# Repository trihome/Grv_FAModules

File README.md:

# FA Extension boards for Grove System

## 1.Introduction

This repository has an interface board for connecting equipment used in the factory to Seeed Studio's "Grove System".

<http://wiki.seeedstudio.com/Grove_System/>

These modules are used to make the equipment used in the factory (switches, sensors, relays, etc.) Allows you to connect to the GROVE system.

These boards support digital (GPIO), analog, and I2C connection types.

Refer to the READEME file in each directory for more information.

**Note**

Please import this library before using this repository.
<https://github.com/trihome/KiCad_MyLibrary>

**How to make**

[Manual (Japanese only)](https://github.com/trihome/RasPi_PiFA/blob/master/doc/README_pcb.jp.md)

## 2.Line up

|Module|Connection Type |function |
|:---|:---|:---|
|[IOExpander](./IOExpander16ch/)     |I2C     |Isolated input/output via I2C   |
|[DigitalOutput](./DigitalOutput4ch)  |GPIO    |Isolated output  |
|[DigitalInput](./DigitalInput4ch)   |GPIO    |Isolated input   |
|      |    |(We will increase the lineup in the future...)   |
<!--|CurrentSensor  |Analog  |Current measurement using CT  |
|SigTowSensor   |Analog  |Detect tower light status   |
|SimpleUPS      |GPIO    |Manage the power supply to RaspberryPi   |-->

## 3.How to connect to microcomputer board

If your board does not have a Grove connector, obtain a **Grove Expansion Board** to connect your Grove module.

- <http://wiki.seeedstudio.com/Platform/>

### (1)Arduino

- <http://wiki.seeedstudio.com/Base_Shield_V2/>

### (2)Raspberry Pi

- <http://wiki.seeedstudio.com/Grove_Base_Hat_for_Raspberry_Pi/>
- <http://wiki.seeedstudio.com/Grove_Base_Hat_for_Raspberry_Pi_Zero/>

### (3)micro:bit

- <https://www.seeedstudio.com/Grove-Shield-for-micro-bit-v2-0.html>

## 4.License

This is under [CC-BY-SA](https://creativecommons.org/licenses/by-sa/4.0/).

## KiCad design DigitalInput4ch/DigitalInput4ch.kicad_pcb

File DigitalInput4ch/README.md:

# Digital Input 4ch

Digital Input for GROVE Digital.
Isolated inputs.

[Schematic](./img/DigitalInput4ch.pdf)

**Notes**

Please import this library before using this repository.
https://github.com/trihome/KiCad_MyLibrary

## 1.Spec

- 4 isolated inputs.
- [GROVE Digital](https://wiki.seeedstudio.com/Grove_System/#digital) Connector x 2 (2ch x 2 = 4ch)
- Supply 24V power to J5 or J6.
- J3,6 are Input for FA(24V)
  - Recommended Terminal block: [2pin](https://akizukidenshi.com/catalog/g/gP-06307/), [3pin](https://akizukidenshi.com/catalog/g/gP-06308/)
- Selectable Sink(NPN) / Source(PNP) : JP1, JP2
- U1,2,3,4: Photocoupler, you have to choose...

|JP1, JP2|Photocoupler (ex)|
|:--|:--|
|N : Sink(NPN)|[FOD814A300W](https://akizukidenshi.com/catalog/g/gI-06483/), [TLP627](https://akizukidenshi.com/catalog/g/gI-07691/)|
|P : Source(PNP)|[FOD814A300W](https://akizukidenshi.com/catalog/g/gI-06483/)|

## 2.Example of use

<!--
### (1)Terminal block

- Button
  - [IDEC](http://jp.idec.com/ja/p/c10/)
  - [OMRON](https://www.fa.omron.co.jp/products/category/switches/push-buttons_indicator-lamps/)
- Lamp
  - [NIKKEI MFG](http://www.nikkei-mfg.co.jp/product/industry/index.htm)
-->

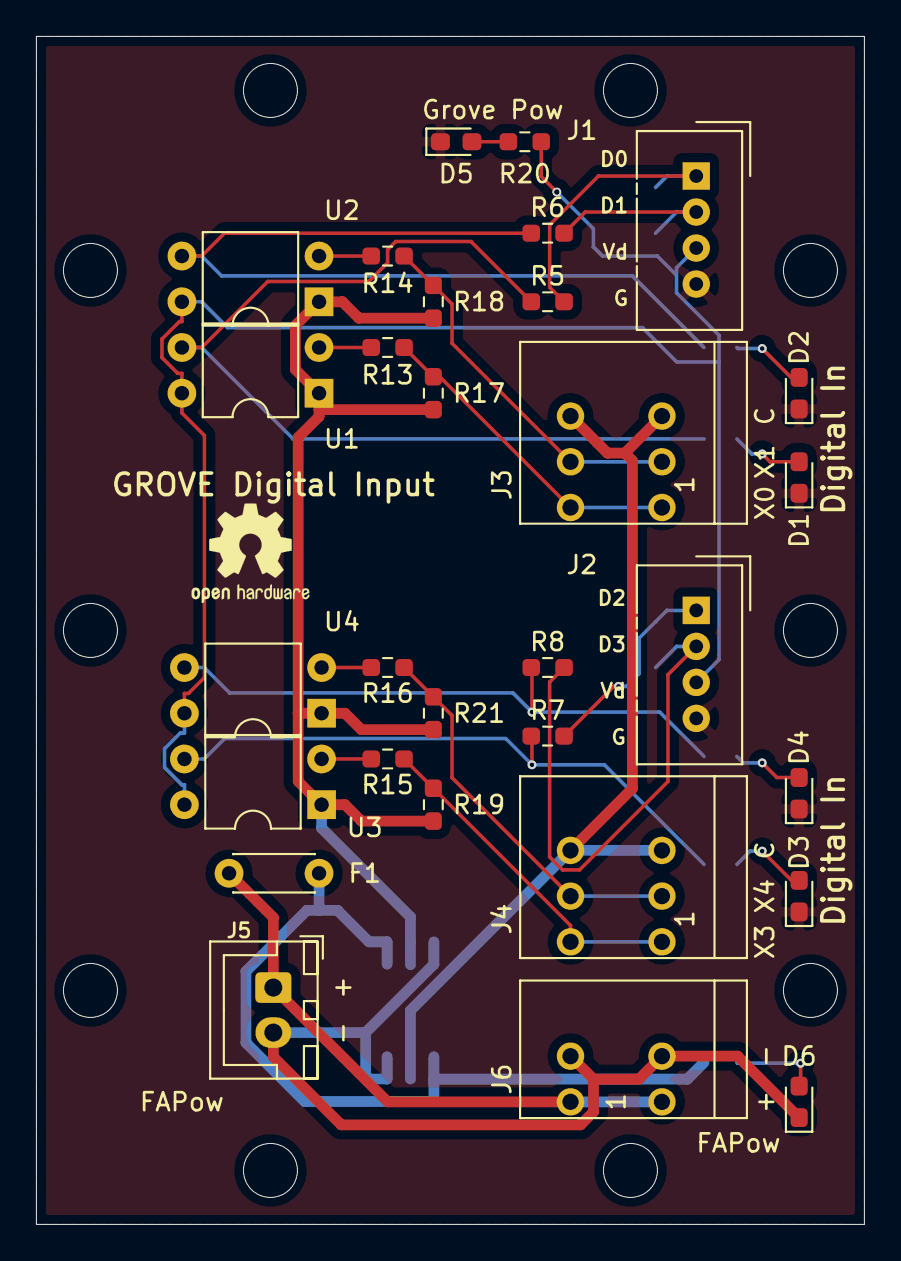
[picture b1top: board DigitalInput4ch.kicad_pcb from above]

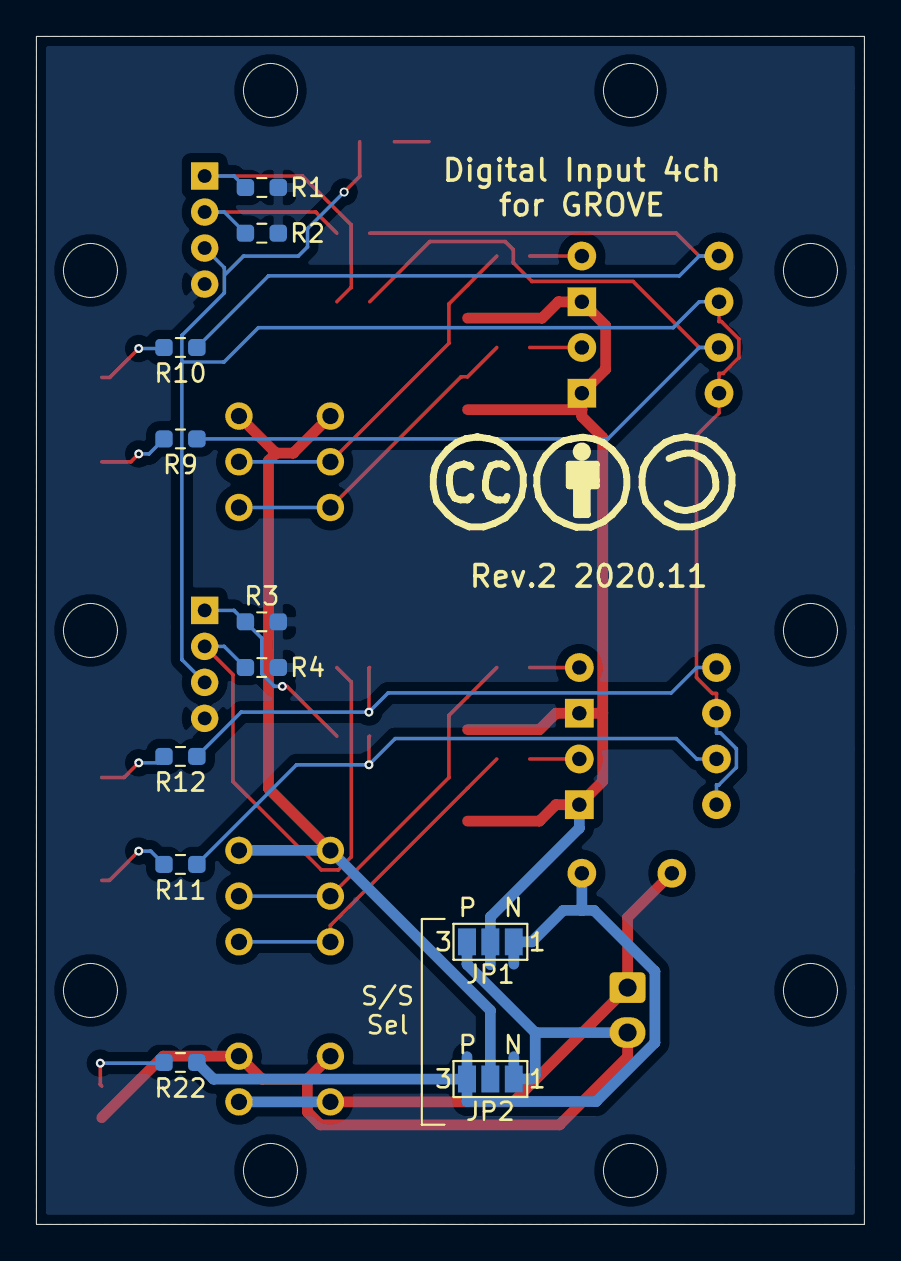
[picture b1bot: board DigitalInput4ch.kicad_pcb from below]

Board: 2 copper layers, 46.0 x 66.0 mm, 53 parts (11 on the bottom side), 29 nets.

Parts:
D1, D2, D3, D4, D5, D6: LED; LED_0603_1608Metric_Pad1.05x0.95mm_HandSolder
F1: 0.5A; C_Disc_D4.3mm_W1.9mm_P5.00mm
J1: GROVE DIn1; NS-Tech_Grove_1x04_P2mm_Vertical
J2: GROVE DIn2; NS-Tech_Grove_1x04_P2mm_Vertical
J3: IN1/2; Terminal_TB401a-1-3-E
J4: OUT3/4; Terminal_TB401a-1-3-E
J5: DC24V IN; JST_XH_B2B-XH-A_1x02_P2.50mm_Vertical
J6: DC24V IN; Terminal_TB401a-1-2-E
JP1: S/S Y+; SolderJumper-3_P1.3mm_Open_Pad1.0x1.5mm_NumberLabels
JP2: S/S Y-; SolderJumper-3_P1.3mm_Open_Pad1.0x1.5mm_NumberLabels
MH1, MH2, MH3, MH4, MH5, MH8, MH9, MH10, MH11, MH12: MountingHole; MountingHole_3mm
MH6: MountingHole; OSHW-Logo2_7.3x6mm_SilkScreen
MH7: MountingHole; CC-BY-SA
R1, R2, R3, R4, R22: 10k; R_0603_1608Metric_Pad0.98x0.95mm_HandSolder
R5, R6, R7, R8: 100; R_0603_1608Metric_Pad0.98x0.95mm_HandSolder
R9, R10, R11, R12: 470; R_0603_1608Metric_Pad0.98x0.95mm_HandSolder
R13, R14, R15, R16, R17, R18, R19, R21: 4.7k; R_0603_1608Metric_Pad0.98x0.95mm_HandSolder
R20: 1k; R_0603_1608Metric_Pad0.98x0.95mm_HandSolder
U1, U2, U3, U4: FOD814A300W; DIP-4_W7.62mm

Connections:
+3V3: J1.3, J2.3, R20.1, U1.4, U2.4, U3.4, U4.4
+24V: F1.1, JP1.1, JP2.3, R22.1
/+24V_: JP1.2, R17.1, R18.1, R19.1, R21.1, U1.1, U2.1, U3.1, U4.1
/GNDD_: J3.5, J3.6, J4.5, J4.6, JP2.2
/IN1: J3.1, J3.2, R13.1, R17.2
/IN2: J3.3, J3.4, R14.1, R18.2
/IN3: J4.1, J4.2, R15.1, R19.2
/IN4: J4.3, J4.4, R16.1, R21.2
GND: D1.1, D2.1, D3.1, D4.1, D5.1, J1.4, J2.4, R1.2, R2.2, R3.2, R4.2
GNDD: D6.1, J5.2, J6.3, J6.4, JP1.3, JP2.1
unnamed: D1.2, R9.2
unnamed: D2.2, R10.2
unnamed: D3.2, R11.2
unnamed: D4.2, R12.2
unnamed: D5.2, R20.2
unnamed: D6.2, R22.2
unnamed: F1.2, J5.1, J6.1, J6.2
unnamed: J1.1, R1.1, R5.2
unnamed: J1.2, R2.1, R6.2
unnamed: J2.1, R3.1, R7.2
unnamed: J2.2, R4.1, R8.2
unnamed: R5.1, R9.1, U1.3
unnamed: R6.1, R10.1, U2.3
unnamed: R7.1, R11.1, U3.3
unnamed: R8.1, R12.1, U4.3
unnamed: R13.2, U1.2
unnamed: R14.2, U2.2
unnamed: R15.2, U3.2
unnamed: R16.2, U4.2

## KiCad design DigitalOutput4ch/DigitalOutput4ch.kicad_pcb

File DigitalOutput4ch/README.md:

# Digital Output 4ch

Digital Output for GROVE Digital.
Isolated outputs.

[Schematic](./img/DigitalOutput4ch.pdf)

**Notes**

Please import this library before using this repository.
https://github.com/trihome/KiCad_MyLibrary

## 1.Spec

- 4 isolated outputs.
- [GROVE Digital](https://wiki.seeedstudio.com/Grove_System/#digital) Connector x 2 (2ch x 2 = 4ch)
- Supply 24V power to J5 or J6.
- J3,6 are Input for FA(24V)
  - Recommended Terminal block: [2pin](https://akizukidenshi.com/catalog/g/gP-06307/), [3pin](https://akizukidenshi.com/catalog/g/gP-06308/)
- Selectable Sink(NPN) / Source(PNP) : JP1, JP2
- U1,2,3,4: Photocoupler, you have to choose...

|JP1, JP2|Photocoupler (ex)|
|:--|:--|
|N : Sink(NPN)|[TLP222A](https://akizukidenshi.com/catalog/g/gI-07672/), [TLP627](https://akizukidenshi.com/catalog/g/gI-07691/)|
|P : Source(PNP)|[TLP222A](https://akizukidenshi.com/catalog/g/gI-07672/)|

## 2.Example of use

<!--
### (1)Terminal block

- Button
  - [IDEC](http://jp.idec.com/ja/p/c10/)
  - [OMRON](https://www.fa.omron.co.jp/products/category/switches/push-buttons_indicator-lamps/)
- Lamp
  - [NIKKEI MFG](http://www.nikkei-mfg.co.jp/product/industry/index.htm)
-->

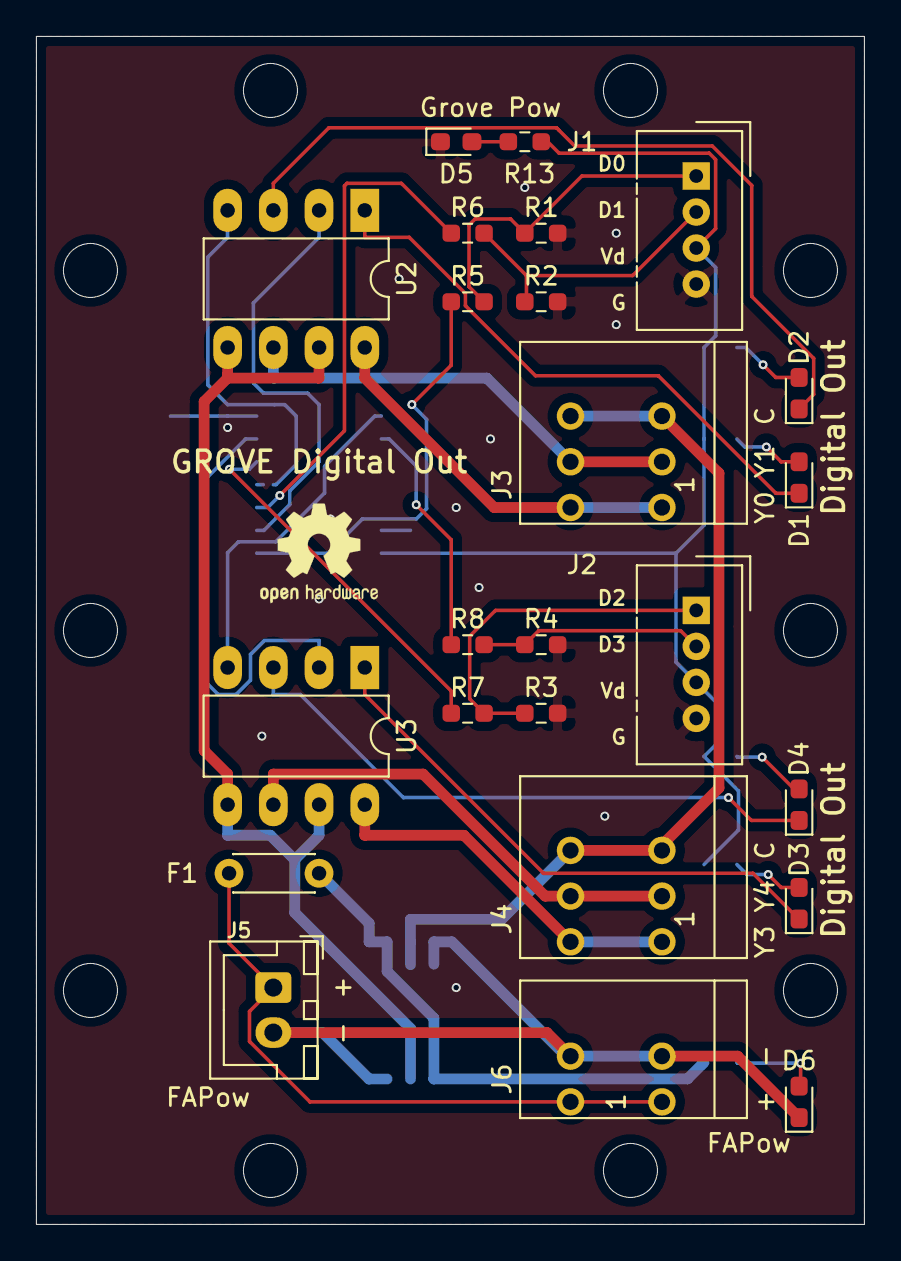
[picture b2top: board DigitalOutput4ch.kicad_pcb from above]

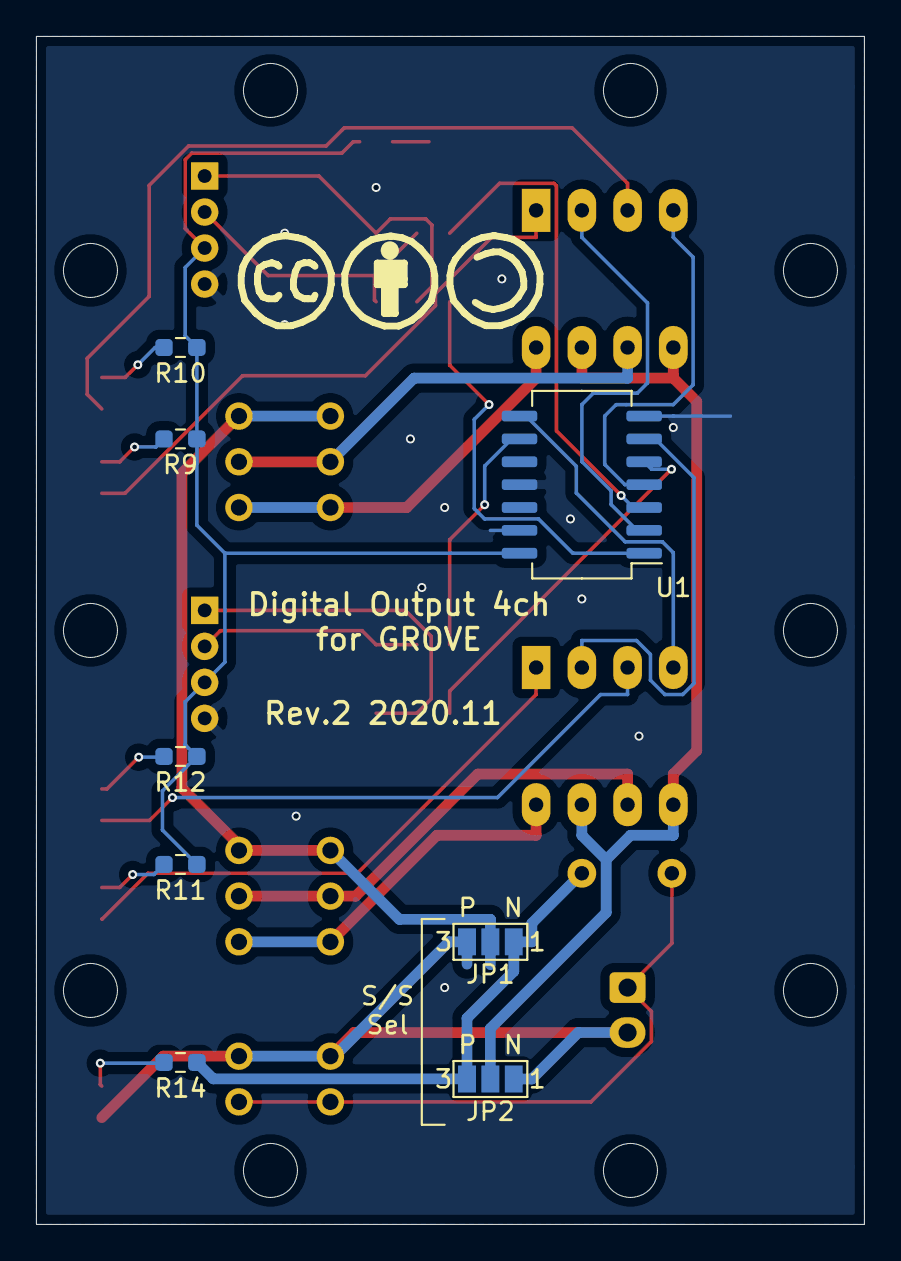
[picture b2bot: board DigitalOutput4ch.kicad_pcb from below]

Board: 2 copper layers, 46.0 x 66.0 mm, 44 parts (8 on the bottom side), 33 nets.

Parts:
D1, D2, D3, D4, D5, D6: LED; LED_0603_1608Metric_Pad1.05x0.95mm_HandSolder
F1: 0.5A; C_Disc_D4.3mm_W1.9mm_P5.00mm
J1, J2: GROVE DOut; NS-Tech_Grove_1x04_P2mm_Vertical
J3: OUT1/2; Terminal_TB401a-1-3-E
J4: OUT3/4; Terminal_TB401a-1-3-E
J5: DC24V IN; JST_XH_B2B-XH-A_1x02_P2.50mm_Vertical
J6: DC24V IN; Terminal_TB401a-1-2-E
JP1: S/S Y+; SolderJumper-3_P1.3mm_Open_Pad1.0x1.5mm_NumberLabels
JP2: S/S Y-; SolderJumper-3_P1.3mm_Open_Pad1.0x1.5mm_NumberLabels
MH1, MH2, MH3, MH4, MH5, MH8, MH9, MH10, MH11, MH12: MountingHole; MountingHole_3mm
MH6: MountingHole; OSHW-Logo2_7.3x6mm_SilkScreen
MH7: MountingHole; CC-BY-SA
R1, R2, R3, R4, R5, R6, R7, R8, R14: 10k; R_0603_1608Metric_Pad0.98x0.95mm_HandSolder
R9, R10, R11, R12: 100; R_0603_1608Metric_Pad0.98x0.95mm_HandSolder
R13: 1k; R_0603_1608Metric_Pad0.98x0.95mm_HandSolder
U1: 74HC14; SO-14_5.3x10.2mm_P1.27mm
U2, U3: TLP627-2; DIP-8_W7.62mm_LongPads

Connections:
+3V3: J1.3, J2.3, R9.1, R10.1, R11.1, R12.1, R13.1, U1.14
+24V: F1.1, JP1.1, JP2.3, R14.1
/+24V_: J3.5, J3.6, J4.5, J4.6, JP1.2
/GNDD_: JP2.2, U2.5, U2.7, U3.5, U3.7
/OUT1: J3.1, J3.2, U2.8
/OUT2: J3.3, J3.4, U2.6
/OUT3: J4.1, J4.2, U3.8
/OUT4: J4.3, J4.4, U3.6
GND: D5.1, J1.4, J2.4, R1.2, R2.2, R3.2, R4.2, U1.7, U1.11, U1.13
GNDD: D6.1, J5.2, J6.3, J6.4, JP1.3, JP2.1
unnamed: D1.1, U2.1
unnamed: D1.2, R9.2
unnamed: D2.1, U2.3
unnamed: D2.2, R10.2
unnamed: D3.1, U3.1
unnamed: D3.2, R11.2
unnamed: D4.1, U3.3
unnamed: D4.2, R12.2
unnamed: D5.2, R13.2
unnamed: D6.2, R14.2
unnamed: F1.2, J5.1, J6.1, J6.2
unnamed: J1.1, R1.1, R5.2
unnamed: J1.2, R2.1, R6.2
unnamed: J2.1, R3.1, R7.2
unnamed: J2.2, R4.1, R8.2
unnamed: R5.1, U1.1
unnamed: R6.1, U1.3
unnamed: R7.1, U1.5
unnamed: R8.1, U1.9
unnamed: U1.2, U2.2
unnamed: U1.4, U2.4
unnamed: U1.6, U3.2
unnamed: U1.8, U3.4

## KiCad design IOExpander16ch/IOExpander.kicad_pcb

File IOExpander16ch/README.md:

# IO Expander 16ch

IO Expander for GROVE I2C.
Isolated inputs and outputs.

[Schematic](./img/IOExpander16ch.pdf)

**Notes**

Please import this library before using this repository.
https://github.com/trihome/KiCad_MyLibrary

## 1.Spec

- 8 isolated inputs and 8 isolated outputs.
- I/O Expander : MCP23017
  - Select I2C address, J4,J5,J6.
  - I2C signal input to J7 (GROVE I2C).
  - INT A, B Pins are output to J8 (GROVE Digital).
- Supply 24V power to J3.
- J1 is Input / Output for FA(24V)
  - Recommended [Terminal block](https://www.togi.co.jp/product/interface/1072/) and [Cables](https://www.togi.co.jp/product/harness-cable/2661/) or QI(2550)connectors.
- Selectable Sink(NPN) / Source(PNP) : J9(Input), J10(Output)
  - IC1: Transistor array, you have to choose.
    - J10 = [Sink(NPN)](http://akizukidenshi.com/catalog/g/gI-10669/)
    - J10 = [Source(PNP)](http://akizukidenshi.com/catalog/g/gI-10957/)
- If you want to communicate with a distant location, add this board.
- [SparkFun Differential I2C Breakout - PCA9615](https://www.switch-science.com/catalog/3907/)

## 2.Example of use

### (1)Terminal block

- Terminal block (34 pin)
  - [Screw connection](https://www.togi.co.jp/product/interface/958/)
  - [Push-in connection(Ferrules)](https://www.togi.co.jp/product/interface/1086)
- [Cables](https://www.togi.co.jp/series/harness-cable/284/)
- Button
  - [IDEC](http://jp.idec.com/ja/p/c10/)
  - [OMRON](https://www.fa.omron.co.jp/products/category/switches/push-buttons_indicator-lamps/)
- Lamp
  - [NIKKEI MFG](http://www.nikkei-mfg.co.jp/product/industry/index.htm)

### (2)Communicate with a device in a remote location

- [SparkFun Differential I2C Breakout - PCA9615](https://www.switch-science.com/catalog/3907/)
  - Connect to J12.
- Ethernet Cables (MAX 30 m)

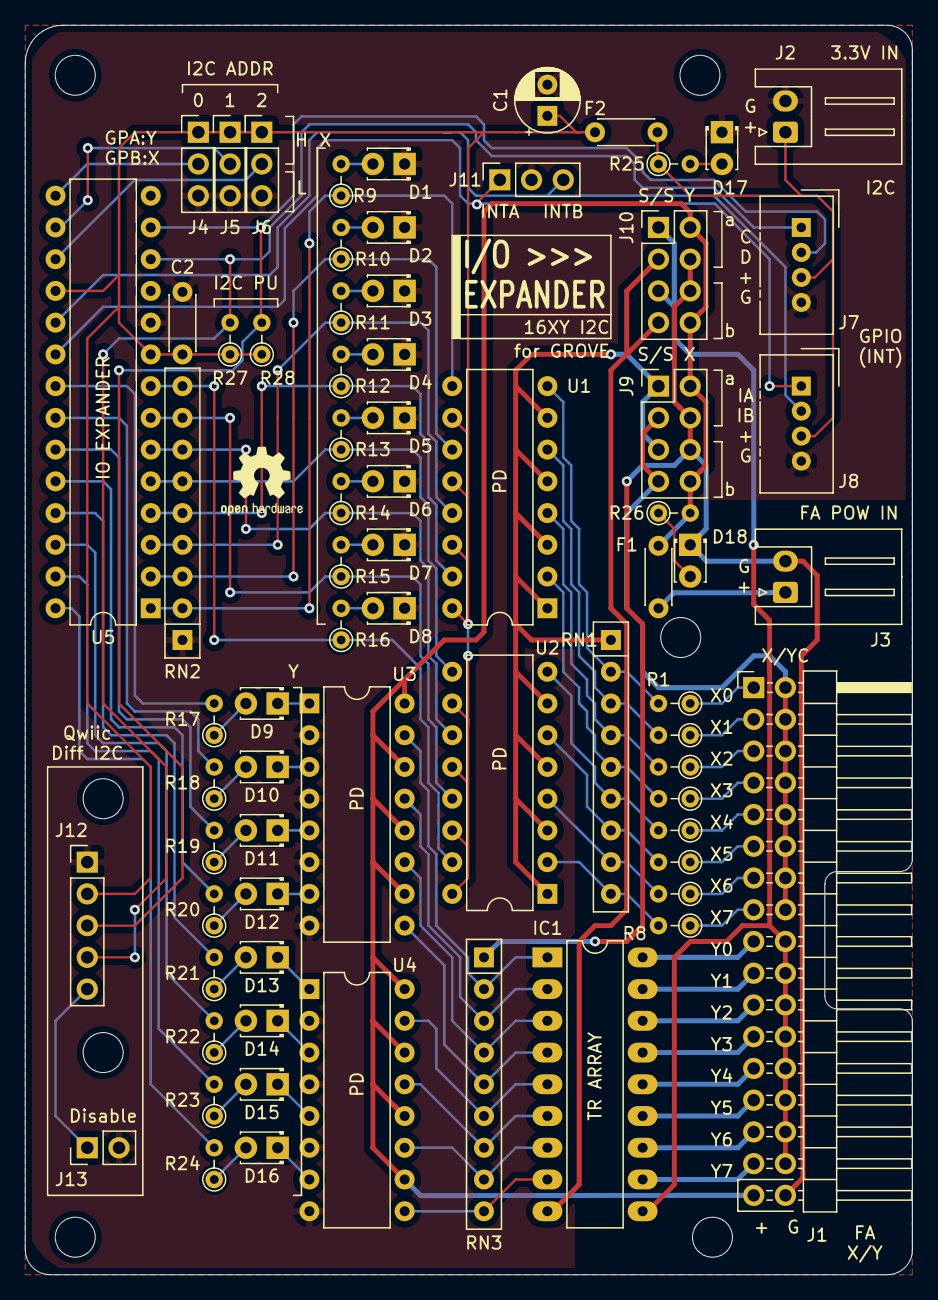
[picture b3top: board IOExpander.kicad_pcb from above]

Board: 2 copper layers, 71.0 x 100.0 mm, 81 parts (0 on the bottom side), 92 nets.

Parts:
C1: 100u; CP_Radial_D5.0mm_P2.50mm
C2: 0.1u; C_Disc_D4.3mm_W1.9mm_P5.00mm
D1, D2, D3, D4, D5, D6, D7, D8: LED(G); LED_D1.8mm_W3.3mm_H2.4mm
D9, D10, D11, D12, D13, D14, D15, D16: LED(Y); LED_D1.8mm_W3.3mm_H2.4mm
D17: LED(R); LED_D1.8mm_W3.3mm_H2.4mm
D18: LED(Or); LED_D1.8mm_W3.3mm_H2.4mm
F1: 0.25A(MAX0.5); C_Disc_D4.3mm_W1.9mm_P5.00mm
F2: 0.17A(MAX0.34); C_Disc_D4.3mm_W1.9mm_P5.00mm
H1, H2, H3, H4, H7, H8, H9: MountingHole; MountingHole_3.2mm_M3
H5: MountingHole; OSHW-Logo2_7.3x6mm_SilkScreen
H6: MountingHole; CC-BY-SA
IC1: TBD62083APG; DIP-18_W7.62mm_LongPads
J1: FA IN/OUT; PinHeader_2x17_P2.54mm_Horizontal
J2: Con Power In; JST_XH_S2B-XH-A_1x02_P2.50mm_Horizontal
J3: FA Power In; JST_XH_S2B-XH-A_1x02_P2.50mm_Horizontal
J4, J5, J6: Conn_01x03; PinHeader_1x03_P2.54mm_Vertical
J7: I2C; NS-Tech_Grove_1x04_P2mm_Vertical
J8: INT; NS-Tech_Grove_1x04_P2mm_Vertical
J9: S/S X; PinHeader_2x04_P2.54mm_Vertical
J10: S/S Y; PinHeader_2x04_P2.54mm_Vertical
J11: INT Check; PinSocket_1x03_P2.54mm_Vertical
J12: Qwiic DiffI2C; PinHeader_1x05_P2.54mm_Vertical
J13: Quiic Disable; PinHeader_1x02_P2.54mm_Vertical
R1, R2, R3, R4, R5, R6, R7, R8, R26: 4.7k; R_Axial_DIN0204_L3.6mm_D1.6mm_P2.54mm_Vertical
R9, R10, R11, R12, R13, R14, R15, R16, R25, R27, R28: 1k; R_Axial_DIN0204_L3.6mm_D1.6mm_P2.54mm_Vertical
R17, R18, R19, R20, R21, R22, R23, R24: 33; R_Axial_DIN0204_L3.6mm_D1.6mm_P2.54mm_Vertical
RN1, RN2: 4.7k; R_Array_SIP9
RN3: 10k; R_Array_SIP9
U1, U2, U3, U4: TLP627-4; DIP-16_W7.62mm
U5: MCP23017_SP; DIP-28_W7.62mm

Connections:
+3V3: C1.1, C2.1, F2.2, J4.1, J5.1, J6.1, J12.2, R27.1, R28.1, U1.10, U1.12, U1.14, U1.16, U2.10, U2.12, U2.14, U2.16, U5.9, U5.18
+24V: F1.2, J1.33, J9.2, J9.8, J10.2, J10.8, R26.2, U3.10, U3.12, U3.14, U3.16, U4.10, U4.12, U4.14, U4.16
/+24V_X: J9.1, J9.5, RN1.1, U1.1, U1.3, U1.5, U1.7, U2.1, U2.3, U2.5, U2.7
/+24V_Y: IC1.10, J1.18, J1.20, J1.22, J1.24, J1.26, J1.28, J1.30, J1.32, J10.1, J10.5
/A0: J4.2, U5.15
/A1: J5.2, U5.16
/A2: J6.2, U5.17
/CON_VDD: F2.1, J2.1, J7.3, J8.3, R25.1
/FA_VDD: F1.1, J3.1
/GNDD_X: J1.2, J1.4, J1.6, J1.8, J1.10, J1.12, J1.14, J1.16, J9.3, J9.7
/GNDD_Y: IC1.9, J10.3, J10.7
/GPA0: R17.2, U5.21
/GPA1: R18.2, U5.22
/GPA2: R19.2, U5.23
/GPA3: R20.2, U5.24
/GPA4: R21.2, U5.25
/GPA5: R22.2, U5.26
/GPA6: R23.2, U5.27
/GPA7: R24.2, U5.28
/GPB0: R9.1, RN2.2, U1.9, U5.1
/GPB1: R10.1, RN2.3, U1.11, U5.2
/GPB2: R11.1, RN2.4, U1.13, U5.3
/GPB3: R12.1, RN2.5, U1.15, U5.4
/GPB4: R13.1, RN2.6, U2.9, U5.5
/GPB5: R14.1, RN2.7, U2.11, U5.6
/GPB6: R15.1, RN2.8, U2.13, U5.7
/GPB7: R16.1, RN2.9, U2.15, U5.8
/INTA: J8.1, J11.1, U5.20
/INTB: J8.2, J11.3, U5.19
/SCL: J7.1, J12.4, R27.2, U5.12
/SDA: J7.2, J12.3, R28.2, U5.13
/Xo00: J1.1, R1.1
/Xo01: J1.3, R2.1
/Xo02: J1.5, R3.1
/Xo03: J1.7, R4.1
/Xo04: J1.9, R5.1
/Xo05: J1.11, R6.1
/Xo06: J1.13, R7.1
/Xo07: J1.15, R8.1
/Y00: IC1.1, RN3.2, U3.15
/Y01: IC1.2, RN3.3, U3.13
/Y02: IC1.3, RN3.4, U3.11
/Y03: IC1.4, RN3.5, U3.9
/Y04: IC1.5, RN3.6, U4.15
/Y05: IC1.6, RN3.7, U4.13
/Y06: IC1.7, RN3.8, U4.11
/Y07: IC1.8, RN3.9, U4.9
/Yo00: IC1.18, J1.17
/Yo01: IC1.17, J1.19
/Yo02: IC1.16, J1.21
/Yo03: IC1.15, J1.23
/Yo04: IC1.14, J1.25
/Yo05: IC1.13, J1.27
/Yo06: IC1.12, J1.29
/Yo07: IC1.11, J1.31
GND: C1.2, C2.2, D1.1, D2.1, D3.1, D4.1, D5.1, D6.1, D7.1, D8.1, D17.1, J2.2, J4.3, J5.3, J6.3, J7.4, J8.4, J11.2, J12.1, J13.2, RN2.1, U3.2, U3.4, U3.6, U3.8, U4.2, U4.4, U4.6, U4.8, U5.10
GNDD: D18.1, J1.34, J3.2, J9.4, J9.6, J10.4, J10.6, RN3.1
unnamed: D1.2, R9.2
unnamed: D2.2, R10.2
unnamed: D3.2, R11.2
unnamed: D4.2, R12.2
unnamed: D5.2, R13.2
unnamed: D6.2, R14.2
unnamed: D7.2, R15.2
unnamed: D8.2, R16.2
unnamed: D9.1, U3.1
unnamed: D9.2, R17.1
unnamed: D10.1, U3.3
unnamed: D10.2, R18.1
unnamed: D11.1, U3.5
unnamed: D11.2, R19.1
unnamed: D12.1, U3.7
unnamed: D12.2, R20.1
unnamed: D13.1, U4.1
unnamed: D13.2, R21.1
unnamed: D14.1, U4.3
unnamed: D14.2, R22.1
unnamed: D15.1, U4.5
unnamed: D15.2, R23.1
unnamed: D16.1, U4.7
unnamed: D16.2, R24.1
unnamed: D17.2, R25.2
unnamed: D18.2, R26.1
unnamed: J12.5, J13.1
unnamed: R1.2, RN1.2, U1.8
unnamed: R2.2, RN1.3, U1.6
unnamed: R3.2, RN1.4, U1.4
unnamed: R4.2, RN1.5, U1.2
unnamed: R5.2, RN1.6, U2.8
unnamed: R6.2, RN1.7, U2.6
unnamed: R7.2, RN1.8, U2.4
unnamed: R8.2, RN1.9, U2.2

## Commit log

2020-07-11 Add files.
2020-07-11 Add files.(IO Expander 16ch)
2020-07-11 Fix typo in docs.
2020-12-17 Add files. (Digital Input 4ch, Output 4ch)

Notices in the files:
parts and their libraries:
Creative Commons Licence
